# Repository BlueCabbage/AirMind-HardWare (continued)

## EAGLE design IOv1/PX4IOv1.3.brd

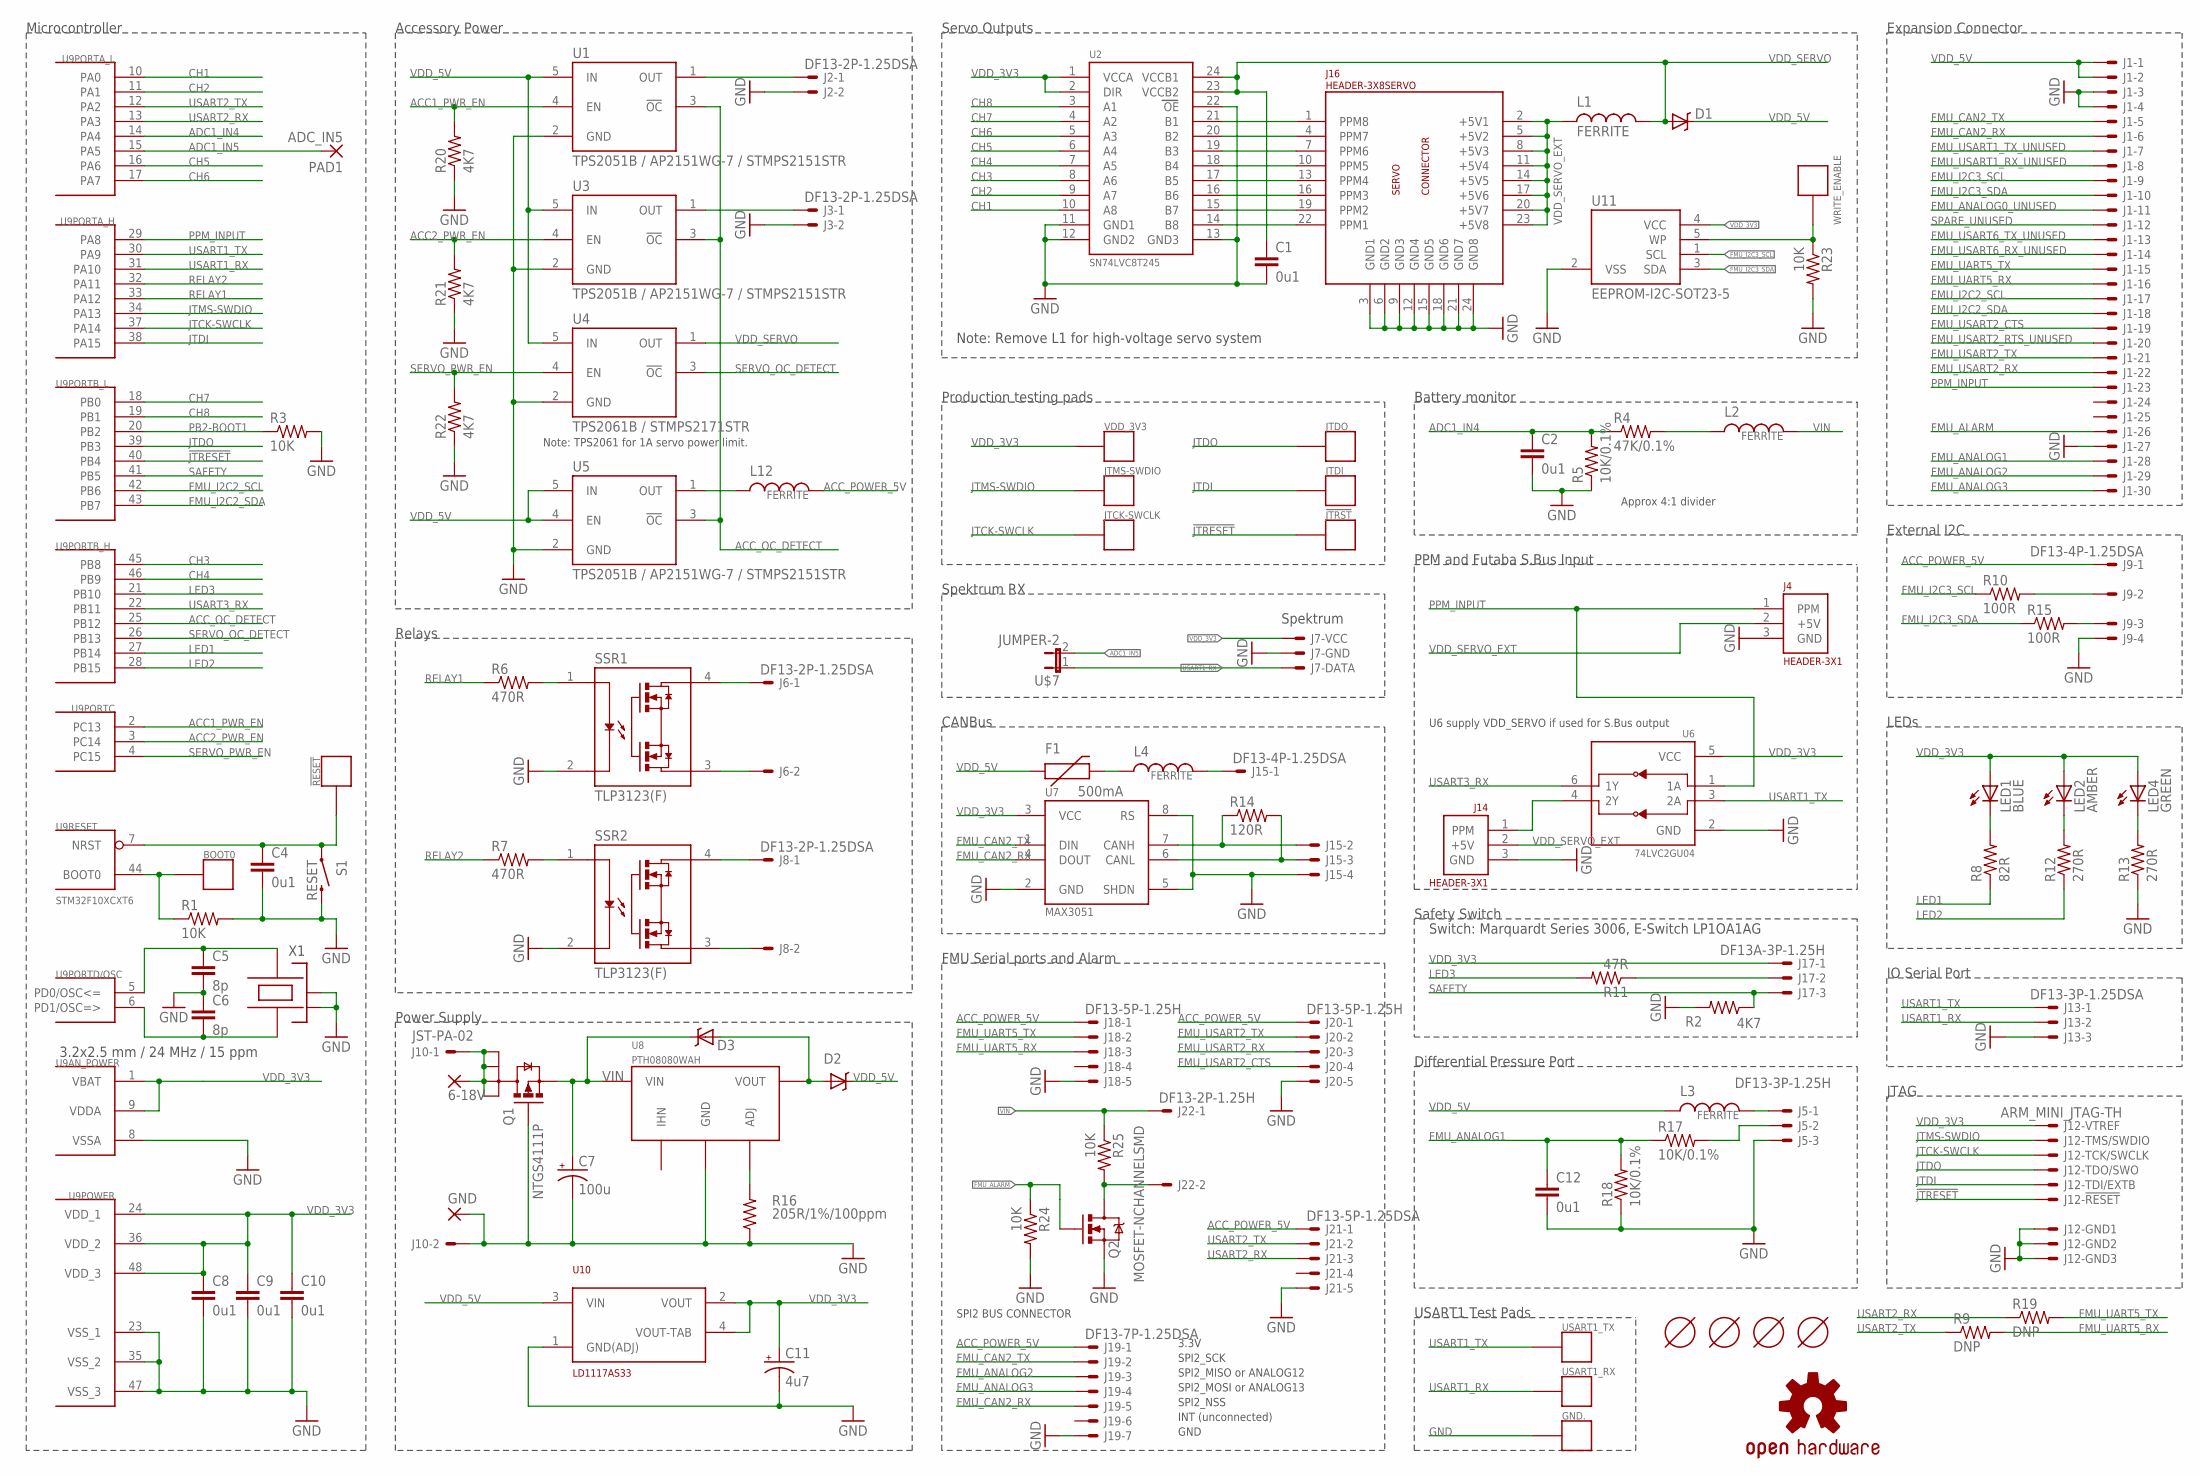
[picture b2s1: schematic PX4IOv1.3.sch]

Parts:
6-18V: WIREPADSMD3,5-2; 3,5-2; PARTNO *
!JTRST: PAD.04; PAD.04X.04; PARTNO *
!RESET: PAD.03; PAD.03X.03; PARTNO *
BOOT0: PAD.04; PAD.04X.04; PARTNO *
C1, C2, C4, C8, C9, C10, C12: 0u1; 0402-CAP; PARTNO CC0402ZRY5V7BB104
C5, C6: 8p; 0402-CAP; PARTNO C1005C0G1H080C
C7: 100u; EIA7343; PARTNO T491X107K025ZT
C11: 4u7; EIA3216; PARTNO T491A475K010AT
D1, D2: BAT 60A E6327; MICROSMP; PARTNO BAT 60A E6327
D3: MSS1P4-M3/89A; MICROSMP; PARTNO MSS1P4-M3/89A
F1: 500mA; 0603; PARTNO MF-FSMF050X-2
GND: WIREPADSMD3,5-2; 3,5-2; PARTNO *
GND.: PAD.04; PAD.04X.04; PARTNO *
J1: HEADER_2X15-REV; HEADER_2MM_2X15_REVERSE; PARTNO 951230-2520-AR-PR
J2, J3, J6, J8: DF13-2P-1.25DSA; PARTNO DF13-2P-1.25DSA
J4, J14: HEADER-3X1; 3X1RA; PARTNO 53047-02
J5: DF13-3P-1.25H; DF13A-3P-1.25H; PARTNO DF13-3P-1.25H(20)
J7: CONN_SPEKTRUM_RX-TH; B3B-ZR; PARTNO B3B-ZR
J9, J15: DF13-4P-1.25DSA; PARTNO DF13-4P-1.25DSA
J10: JST-PA-02; S02B-PASK-2; PARTNO S02B-PASK-2
J12: ARM_MINI_JTAG-TH; FTSH-105-01-XXX-DV; PARTNO M50-3900542
J13: DF13-3P-1.25DSA; PARTNO DF13-3P-1.25DSA
J16: HEADER-3X8SERVO; 3X8RA; PARTNO *
J17: DF13A-3P-1.25H; PARTNO DF13A-3P-1.25H(20)
J18, J20: DF13-5P-1.25H; DF13A-5P-1.25H; PARTNO DF13A-5P-1.25H(20)
J19: DF13-7P-1.25DSA; PARTNO DF13-7P-1.25DSA(20)
J21: DF13-5P-1.25DSA; PARTNO DF13-5P-1.25DSA(20)
J22: DF13-2P-1.25H; DF13A-2P-1.25H; PARTNO DF13-2P-1.25H(20)
JTCK-SWCLK: PAD.04; PAD.04X.04; PARTNO *
JTDI: PAD.04; PAD.04X.04; PARTNO *
JTDO: PAD.04; PAD.04X.04; PARTNO *
JTMS-SWDIO: PAD.04; PAD.04X.04; PARTNO *
L1, L2, L3, L4, L12: FERRITE; 0402-IND; PARTNO BKP1005HS121-T
LED1: BLUE; LED-0603; PARTNO LNJ937W8CRA
LED2: AMBER; LED-0603; PARTNO LNJ437W84RA
LED4: GREEN; LED-0603; PARTNO LNJ337W83RA
PAD1: ADC_IN5; PAD-2.5-1.8
Q1: NTGS4111P; TSOP-6; PARTNO NTGS4111P
Q2: MOSFET-NCHANNELSMD; SOT23-3; PARTNO ZXMS6004FFTA
R1, R3, R23, R24, R25: 10K; 0402-RES; PARTNO RMCF0402FT10K0
R2, R20, R21, R22: 4K7; 0402-RES; PARTNO RMCF0402JT4K70
R4: 47K/0.1%; 0402-RES; PARTNO RC0402FR-0747KL
R5, R17, R18: 10K/0.1%; 0402-RES; PARTNO RMCF0402FT10K0
R6, R7: 470R; 0402-RES; PARTNO RMCF0402JT470R
R8: 82R; 0402-RES; PARTNO MCR01MZPJ820
R9, R19: DNP; 0402-RES; PARTNO RMCF0402FT10K0
R10, R15: 100R; 0402-RES; PARTNO RMCF0402JT100R
R11: 47R; 0402-RES; PARTNO RMCF0402JT47R0
R12, R13: 270R; 0402-RES; PARTNO MCR01MZPJ271
R14: 120R; 0402-RES; PARTNO P120JCT-ND
R16: 205R/1%/100ppm; 0402-RES; PARTNO ERJ-2RKF2050X
S1: RESET; EVQP7J01K; PARTNO EVQP7J01K
SSR1, SSR2: TLP3123(F); SOP4-2.54; PARTNO TLP3123(F)
U1, U3, U5: TPS2051B / AP2151WG-7 / STMPS2151STR; SOT23-5L; PARTNO AP2151WG-7
U2: SN74LVC8T245; R-PDSO-G24; PARTNO SN74LVC8T245DBQR
U4: TPS2061B / STMPS2171STR; SOT23-5L; PARTNO STMPS2171STR
U6: 74LVC2GU04; SOT363_PHILIPS; PARTNO 74LVC2GU04GW,125
U7: MAX3051; SO08; PARTNO MAX3051ESA+
U8: PTH08080WAH; PTH08080W_TH; PARTNO PTH08080WAH
U9: STM32F10XCXT6; TQFP48; PARTNO STM32F100C8T6B
U10: LD1117AS33; SOT-223; PARTNO LD1117AS33
U11: EEPROM-I2C-SOT23-5; SOT23-5; PARTNO 24LC01BT-I/OT
U$1: OSHW-LOGOS; OSHW-LOGO-S
U$2, U$3, U$4, U$5: MOUNT-HOLE3.1MM; MOUNT-HOLE3.1; PARTNO *
U$7: JUMPER-2; SJ_2
USART1_RX, USART1_TX: PAD.04; PAD.04X.04; PARTNO *
VDD_3V3: PAD.04; PAD.04X.04; PARTNO *
WRITE_ENABLE: PAD.04; PAD.04X.04; PARTNO *
X1: 3.2x2.5 mm / 24 MHz / 15 ppm; OSCILLATOR-3.2X2.5; PARTNO NX3225SA-24.000000MHZ

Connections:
!JTRESET: !JTRST.P$1, J12.10, U9.40 (PB4)
ACC1_PWR_EN: R20.2, U1.4 (EN), U9.2 (PC13)
ACC2_PWR_EN: R21.2, U3.4 (EN), U9.3 (PC14)
ACC_OC_DETECT: U1.3 (!OC), U3.3 (!OC), U5.3 (!OC), U9.25 (PB12)
ACC_POWER_5V: J9.1, J18.1, J19.1, J20.1, J21.1, L12.2
ADC1_IN4: C2.1, R4.1, R5.2, U9.14 (PA4)
ADC1_IN5: PAD1.P$1, U9.15 (PA5), U$7.2
BOOT0: BOOT0.P$1, R1.1, U9.44 (BOOT0)
CH1: U2.10 (A8), U9.10 (PA0)
CH2: U2.9 (A7), U9.11 (PA1)
CH3: U2.8 (A6), U9.45 (PB8)
CH4: U2.7 (A5), U9.46 (PB9)
CH5: U2.6 (A4), U9.16 (PA6)
CH6: U2.5 (A3), U9.17 (PA7)
CH7: U2.4 (A2), U9.18 (PB0)
CH8: U2.3 (A1), U9.19 (PB1)
FMU_ALARM: J1.26, Q2.1 (G), R24.1
FMU_ANALOG0_UNUSED: J1.11
FMU_ANALOG1: C12.1, J1.28, R17.1, R18.2
FMU_ANALOG2: J1.29, J19.3
FMU_ANALOG3: J1.30, J19.4
FMU_CAN2_RX: J1.6, J19.5, U7.4 (DOUT)
FMU_CAN2_TX: J1.5, J19.2, U7.1 (DIN)
FMU_I2C2_SCL: J1.17, U9.42 (PB6)
FMU_I2C2_SDA: J1.18, U9.43 (PB7)
FMU_I2C3_SCL: J1.9, R10.1, U11.1 (SCL)
FMU_I2C3_SDA: J1.10, R15.1, U11.3 (SDA)
FMU_UART5_RX: J1.16, J18.3, R9.2
FMU_UART5_TX: J1.15, J18.2, R19.2
FMU_USART1_RX_UNUSED: J1.8
FMU_USART1_TX_UNUSED: J1.7
FMU_USART2_CTS: J1.19, J20.4
FMU_USART2_RTS_UNUSED: J1.20
FMU_USART2_RX: J1.22, J20.3
FMU_USART2_TX: J1.21, J20.2
FMU_USART6_RX_UNUSED: J1.14
FMU_USART6_TX_UNUSED: J1.13
GND: C1.2, C2.2, C4.2, C5.2, C6.1, C7.C (-), C8.2, C9.2, C10.2, C11.C (-), C12.2, GND.1, GND..P$1, J1.3, J1.4, J1.27, J2.2, J3.2, J4.3 (GND), J5.3, J7.2, J9.4, J10.2, J12.3, J12.5, J12.9, J13.3, J14.3 (GND), J15.4, J16.3 (GND1), J16.6 (GND2), J16.9 (GND3), J16.12 (GND4), J16.15 (GND5), J16.18 (GND6), J16.21 (GND7), J16.24 (GND8), J18.5, J19.7, J20.5, J21.5, Q1.3 (G), Q2.2 (S), R1.2, R2.2, R3.2, R5.1, R13.1, R16.1, R18.1, R20.1, R21.1, R22.1, R23.2, R24.2, S1.B3 (2), SSR1.2, SSR2.2, U1.2 (GND), U2.11 (GND1), U2.12 (GND2), U2.13 (GND3), U2.22 (OE), U3.2 (GND), U4.2 (GND), U5.2 (GND), U6.2 (GND), U7.2 (GND), U7.5 (SHDN), U7.8 (RS), U8.2 (GND), U9.8 (VSSA), U9.23 (VSS_1), U9.35 (VSS_2), U9.47 (VSS_3), U10.1 (GND(ADJ)), U11.2 (VSS), X1.2 (NC_2), X1.4 (NC_4)
JTCK-SWCLK: J12.4, JTCK-SWCLK.P$1, U9.37 (PA14)
JTDI: J12.8, JTDI.P$1, U9.38 (PA15)
JTDO: J12.6, JTDO.P$1, U9.39 (PB3)
JTMS-SWDIO: J12.2, JTMS-SWDIO.P$1, U9.34 (PA13)
LED1: R8.1, U9.27 (PB14)
LED2: R12.1, U9.28 (PB15)
LED3: R11.2, U9.21 (PB10)
unnamed: R7.2, SSR2.1
unnamed: R6.2, SSR1.1
unnamed: J14.1 (PPM), U6.4 (2Y)
unnamed: L12.1, U5.1 (OUT)
unnamed: C6.2, U9.6 (PD1/OSC=>), X1.1
unnamed: C5.1, U9.5 (PD0/OSC<=), X1.3
unnamed: L2.1, R4.2
unnamed: LED1.C, R8.2
unnamed: R16.2, U8.4 (ADJ)
unnamed: J17.2, R11.1
unnamed: R23.1, U11.5 (WP), WRITE_ENABLE.P$1
unnamed: J22.2, Q2.3 (D), R25.2
unnamed: F1.2, L4.1
unnamed: J5.2, R17.2
unnamed: J8.1, SSR2.4
unnamed: J8.2, SSR2.3
unnamed: J6.2, SSR1.3
unnamed: J6.1, SSR1.4
unnamed: J9.3, R15.2
unnamed: J9.2, R10.2
unnamed: J2.1, U1.1 (OUT)
unnamed: J3.1, U3.1 (OUT)
unnamed: LED2.C, R12.2
unnamed: LED4.C, R13.2
unnamed: J15.2, R14.1, U7.7 (CANH)
unnamed: J15.3, R14.2, U7.6 (CANL)
unnamed: J15.1, L4.2
NRST: !RESET.P$1, C4.1, S1.A1 (1), U9.7 (NRST)
PB2-BOOT1: R3.1, U9.20 (PB2)
PPM1: J16.22 (PPM1), U2.14 (B8)
PPM2: J16.19 (PPM2), U2.15 (B7)
PPM3: J16.16 (PPM3), U2.16 (B6)
PPM4: J16.13 (PPM4), U2.17 (B5)
PPM5: J16.10 (PPM5), U2.18 (B4)
PPM6: J16.7 (PPM6), U2.19 (B3)
PPM7: J16.4 (PPM7), U2.20 (B2)
PPM8: J16.1 (PPM8), U2.21 (B1)
PPM_INPUT: J1.23, J4.1 (PPM), U6.1 (1A), U9.29 (PA8)
RELAY1: R6.1, U9.33 (PA12)
RELAY2: R7.1, U9.32 (PA11)
SAFETY: J17.3, R2.1, U9.41 (PB5)
SERVO_OC_DETECT: U4.3 (!OC), U9.26 (PB13)
SERVO_PWR_EN: R22.2, U4.4 (EN), U9.4 (PC15)
SPARE_UNUSED: J1.12
USART1_RX: J7.1, J13.2, U9.31 (PA10), U$7.1, USART1_RX.P$1
USART1_TX: J13.1, U6.3 (2A), U9.30 (PA9), USART1_TX.P$1
USART2_RX: J21.3, R19.1, U9.13 (PA3)
USART2_TX: J21.2, R9.1, U9.12 (PA2)
USART3_RX: U6.6 (1Y), U9.22 (PB11)
VDD_3V3: C8.1, C9.1, C10.1, C11.A (+), J7.3, J12.1, J17.1, LED1.A, LED2.A, LED4.A, U2.1 (VCCA), U2.2 (DIR), U6.5 (VCC), U7.3 (VCC), U9.1 (VBAT), U9.9 (VDDA), U9.24 (VDD_1), U9.36 (VDD_2), U9.48 (VDD_3), U10.2 (VOUT), U10.4 (VOUT-TAB), U11.4 (VCC), VDD_3V3.P$1
VDD_5V: D1.CATHODE (C), D2.CATHODE (C), F1.1, J1.1, J1.2, L3.1, U1.5 (IN), U3.5 (IN), U4.5 (IN), U5.4 (EN), U5.5 (IN), U10.3 (VIN)
VDD_5V_ANALOG: J5.1, L3.2
VDD_SERVO: C1.1, D1.ANODE (A), L1.2, U2.23 (VCCB2), U2.24 (VCCB1), U4.1 (OUT)
VDD_SERVO_EXT: J4.2 (+5V), J14.2 (+5V), J16.2 (+5V1), J16.5 (+5V2), J16.8 (+5V3), J16.11 (+5V4), J16.14 (+5V5), J16.17 (+5V6), J16.20 (+5V7), J16.23 (+5V8), L1.1
VIN: C7.A (+), D3.CATHODE (C), J22.1, L2.2, Q1.4 (S), R25.1, U8.1 (VIN)
VIN_CONTACT: 6-18V.1, J10.1, Q1.1 (D), Q1.2 (D1), Q1.5 (D2), Q1.6 (D3)
VOUT: D2.ANODE (A), D3.ANODE (A), U8.3 (VOUT)

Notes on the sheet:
Note: Remove L1 for high-voltage servo system
Spektrum
Accessory Power
Relays
Power Supply
Servo Outputs
CANBus
Production testing pads
External I2C
Spektrum RX
JTAG
LEDs
FMU Serial ports and Alarm
Expansion Connector
Microcontroller
Note: TPS2061 for 1A servo power limit.
PPM and Futaba S.Bus Input
Differential Pressure Port
Battery monitor
Approx 4:1 divider
U6 supply VDD_SERVO if used for S.Bus output
IO Serial Port
USART1 Test Pads
Safety Switch
Switch: Marquardt Series 3006, E-Switch LP1OA1AG
3.3V
SPI2_SCK
SPI2_MISO or ANALOG12
SPI2_MOSI or ANALOG13
SPI2_NSS
GND
SPI2 BUS CONNECTOR
INT (unconnected)

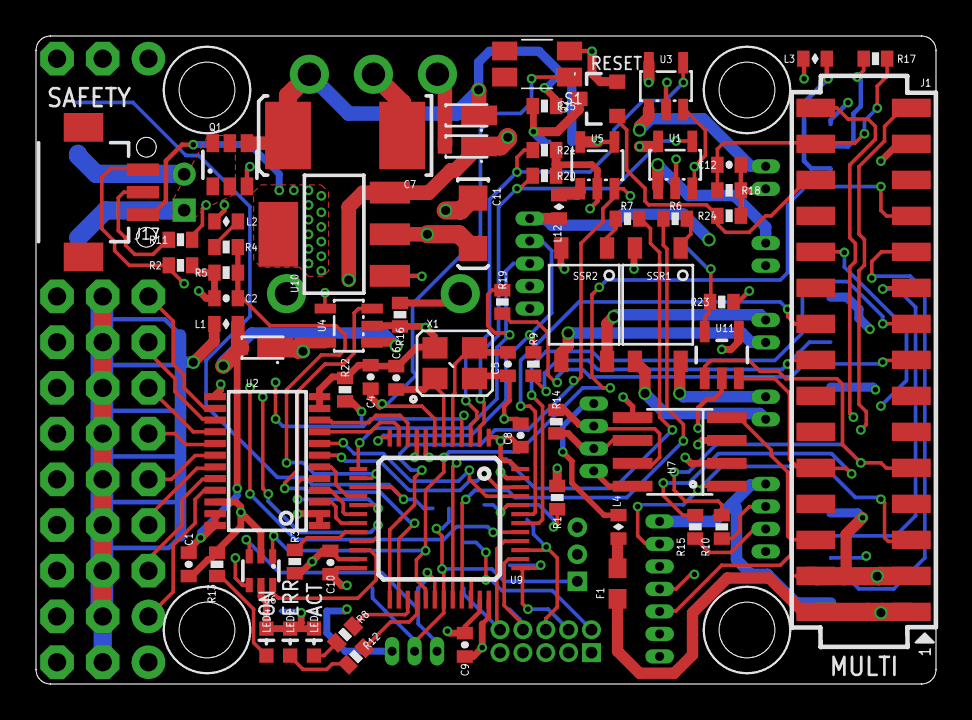
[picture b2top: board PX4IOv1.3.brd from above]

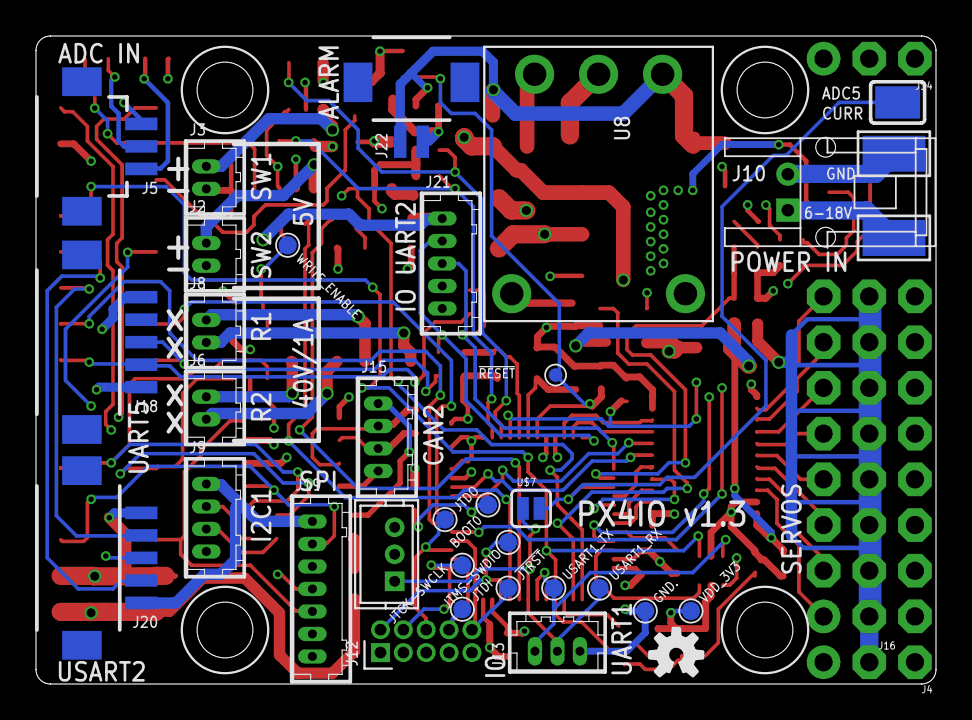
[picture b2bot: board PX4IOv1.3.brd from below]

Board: 4 copper layers, 50.0 x 36.0 mm, 107 parts (37 on the bottom side), 95 nets.

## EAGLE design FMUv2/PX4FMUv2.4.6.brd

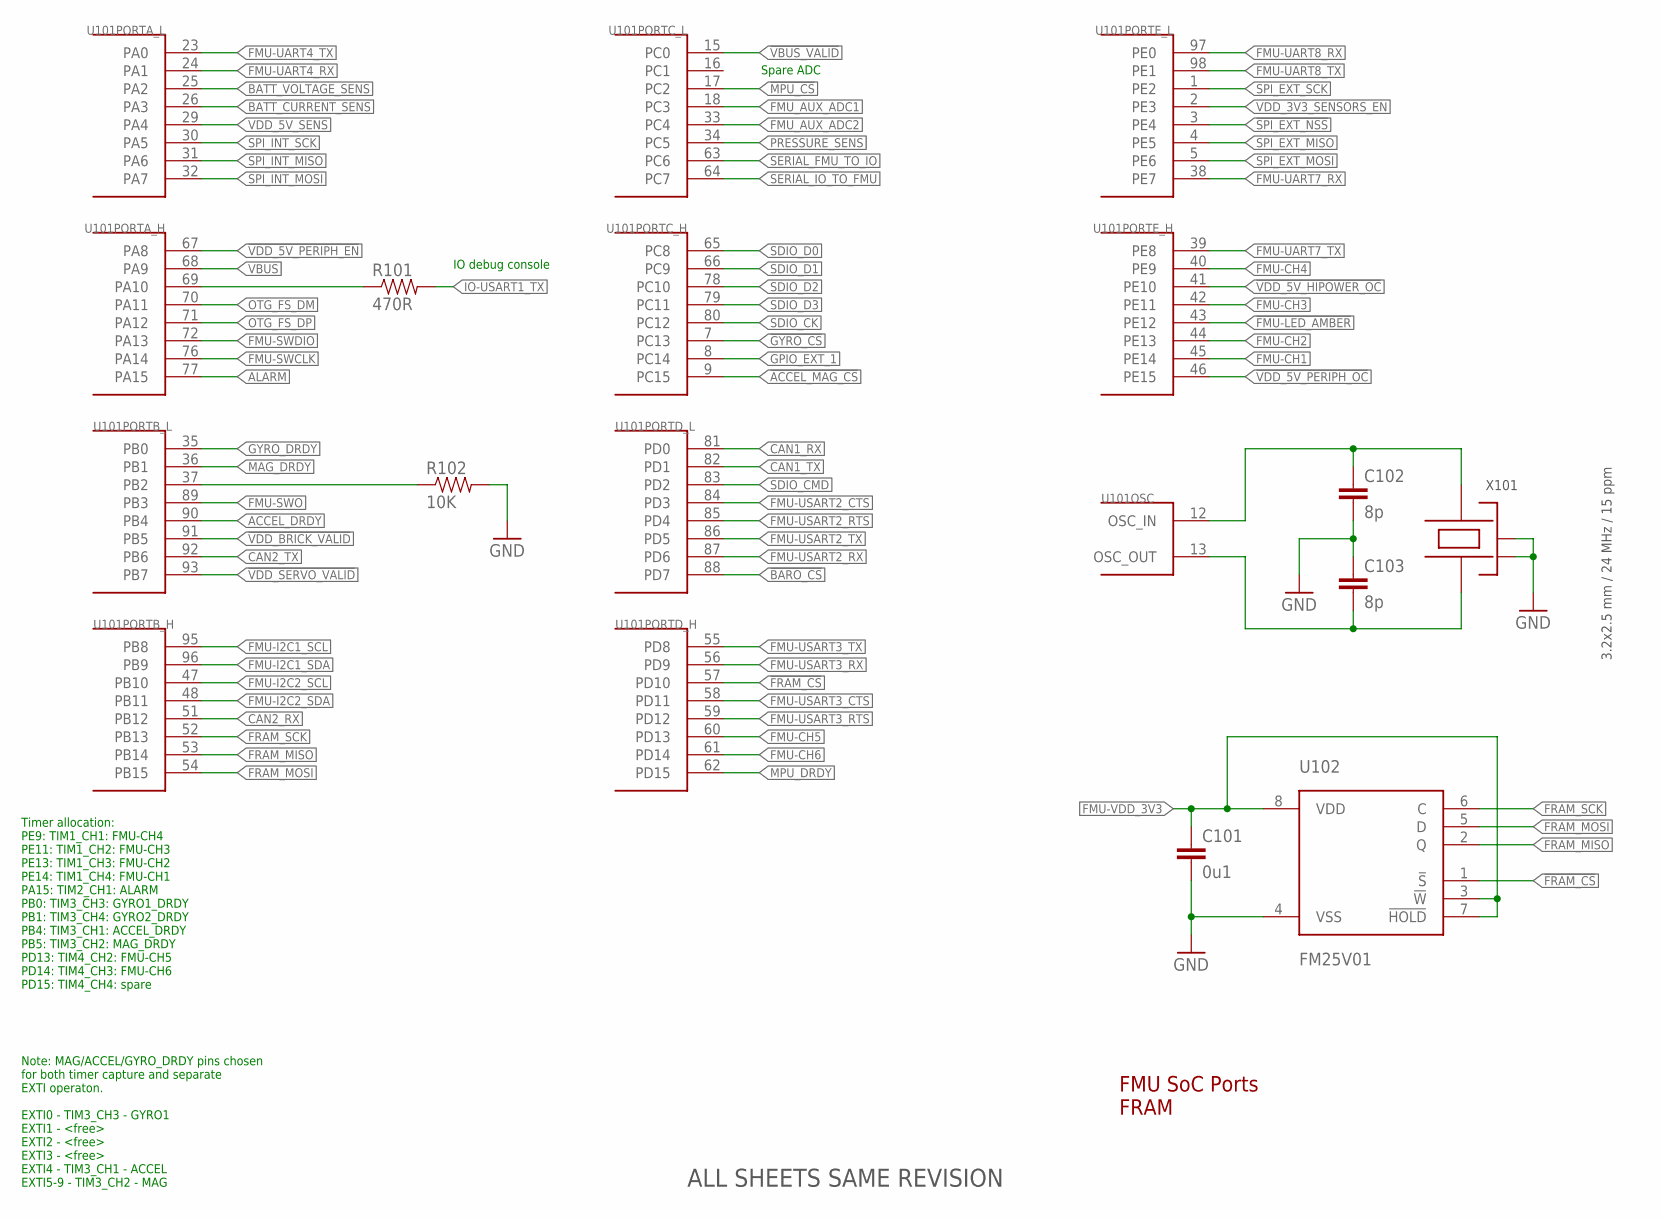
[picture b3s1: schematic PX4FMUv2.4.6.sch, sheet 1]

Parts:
C101: 0u1; 0402-CAP; PARTNO CC0402ZRY5V7BB104
C102, C103: 8p; 0402-CAP; PARTNO C1005C0G1H080C
R101: 470R; 0402-RES; PARTNO RC0402FR-07470RL
R102: 10K; 0402-RES; PARTNO RC0402FR-0710KL
U101: STM32F4X7VX; TQFP100; PARTNO STM32F427VI
U102: FM25V01; SO08; PARTNO FM25V01-G
X101: 3.2x2.5 mm / 24 MHz / 15 ppm; OSCILLATOR-3.2X2.5; PARTNO NX3225SA-24.000000MHZ

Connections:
!ACCEL_MAG_CS: U101.9 (PC15); also elsewhere on the board
!BARO_CS: U101.88 (PD7); also elsewhere on the board
!FMU-LED_AMBER: U101.43 (PE12); also elsewhere on the board
!FRAM_CS: U101.57 (PD10), U102.1 (!S)
!GYRO_CS: U101.7 (PC13); also elsewhere on the board
!MPU_CS: U101.17 (PC2); also elsewhere on the board
!SPI_EXT_NSS: U101.3 (PE4); also elsewhere on the board
!VBUS_VALID: U101.15 (PC0); also elsewhere on the board
!VDD_5V_HIPOWER_OC: U101.41 (PE10); also elsewhere on the board
!VDD_5V_PERIPH_EN: U101.67 (PA8); also elsewhere on the board
!VDD_5V_PERIPH_OC: U101.46 (PE15); also elsewhere on the board
!VDD_BRICK_VALID: U101.91 (PB5); also elsewhere on the board
!VDD_SERVO_VALID: U101.93 (PB7); also elsewhere on the board
ACCEL_DRDY: U101.90 (PB4); also elsewhere on the board
ALARM: U101.77 (PA15); also elsewhere on the board
BATT_CURRENT_SENS: U101.26 (PA3); also elsewhere on the board
BATT_VOLTAGE_SENS: U101.25 (PA2); also elsewhere on the board
CAN1_RX: U101.81 (PD0); also elsewhere on the board
CAN1_TX: U101.82 (PD1); also elsewhere on the board
CAN2_RX: U101.51 (PB12); also elsewhere on the board
CAN2_TX: U101.92 (PB6); also elsewhere on the board
FMU-CH1: U101.45 (PE14); also elsewhere on the board
FMU-CH2: U101.44 (PE13); also elsewhere on the board
FMU-CH3: U101.42 (PE11); also elsewhere on the board
FMU-CH4: U101.40 (PE9); also elsewhere on the board
FMU-CH5: U101.60 (PD13); also elsewhere on the board
FMU-CH6: U101.61 (PD14); also elsewhere on the board
FMU-I2C1_SCL: U101.95 (PB8); also elsewhere on the board
FMU-I2C1_SDA: U101.96 (PB9); also elsewhere on the board
FMU-I2C2_SCL: U101.47 (PB10); also elsewhere on the board
FMU-I2C2_SDA: U101.48 (PB11); also elsewhere on the board
FMU-SWCLK: U101.76 (PA14); also elsewhere on the board
FMU-SWDIO: U101.72 (PA13); also elsewhere on the board
FMU-SWO: U101.89 (PB3); also elsewhere on the board
FMU-UART4_RX: U101.24 (PA1); also elsewhere on the board
FMU-UART4_TX: U101.23 (PA0); also elsewhere on the board
FMU-UART7_RX: U101.38 (PE7); also elsewhere on the board
FMU-UART7_TX: U101.39 (PE8); also elsewhere on the board
FMU-UART8_RX: U101.97 (PE0); also elsewhere on the board
FMU-UART8_TX: U101.98 (PE1); also elsewhere on the board
FMU-USART2_CTS: U101.84 (PD3); also elsewhere on the board
FMU-USART2_RTS: U101.85 (PD4); also elsewhere on the board
FMU-USART2_RX: U101.87 (PD6); also elsewhere on the board
FMU-USART2_TX: U101.86 (PD5); also elsewhere on the board
FMU-USART3_CTS: U101.58 (PD11); also elsewhere on the board
FMU-USART3_RTS: U101.59 (PD12); also elsewhere on the board
FMU-USART3_RX: U101.56 (PD9); also elsewhere on the board
FMU-USART3_TX: U101.55 (PD8); also elsewhere on the board
FMU-VDD_3V3: C101.P$1 (1), U102.3 (!W), U102.7 (!HOLD), U102.8 (VDD); also elsewhere on the board
FMU_AUX_ADC1: U101.18 (PC3); also elsewhere on the board
FMU_AUX_ADC2: U101.33 (PC4); also elsewhere on the board
FRAM_MISO: U101.53 (PB14), U102.2 (Q)
FRAM_MOSI: U101.54 (PB15), U102.5 (D)
FRAM_SCK: U101.52 (PB13), U102.6 (C)
GND: C101.P$2 (2), C102.P$2 (2), C103.P$1 (1), R102.P$2 (2), U102.4 (VSS), X101.2 (NC_2), X101.4 (NC_4); also elsewhere on the board
GPIO_EXT_1: U101.8 (PC14); also elsewhere on the board
GYRO_DRDY: U101.35 (PB0); also elsewhere on the board
IO-USART1_TX: R101.P$2 (2); also elsewhere on the board
MAG_DRDY: U101.36 (PB1); also elsewhere on the board
MPU_DRDY: U101.62 (PD15); also elsewhere on the board
unnamed: C103.P$2 (2), U101.13 (OSC_OUT), X101.1
unnamed: C102.P$1 (1), U101.12 (OSC_IN), X101.3
unnamed: R101.P$1 (1), U101.69 (PA10)
OTG_FS_DM: U101.70 (PA11); also elsewhere on the board
OTG_FS_DP: U101.71 (PA12); also elsewhere on the board
PB2-BOOT1: R102.P$1 (1), U101.37 (PB2)
PRESSURE_SENS: U101.34 (PC5); also elsewhere on the board
SDIO_CK: U101.80 (PC12); also elsewhere on the board
SDIO_CMD: U101.83 (PD2); also elsewhere on the board
SDIO_D0: U101.65 (PC8); also elsewhere on the board
SDIO_D1: U101.66 (PC9); also elsewhere on the board
SDIO_D2: U101.78 (PC10); also elsewhere on the board
SDIO_D3: U101.79 (PC11); also elsewhere on the board
SERIAL_FMU_TO_IO: U101.63 (PC6); also elsewhere on the board
SERIAL_IO_TO_FMU: U101.64 (PC7); also elsewhere on the board
SPI_EXT_MISO: U101.4 (PE5); also elsewhere on the board
SPI_EXT_MOSI: U101.5 (PE6); also elsewhere on the board
SPI_EXT_SCK: U101.1 (PE2); also elsewhere on the board
SPI_INT_MISO: U101.31 (PA6); also elsewhere on the board
SPI_INT_MOSI: U101.32 (PA7); also elsewhere on the board
SPI_INT_SCK: U101.30 (PA5); also elsewhere on the board
VBUS: U101.68 (PA9); also elsewhere on the board
VDD_3V3_SENSORS_EN: U101.2 (PE3); also elsewhere on the board
VDD_5V_SENS: U101.29 (PA4); also elsewhere on the board

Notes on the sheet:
FMU SoC Ports FRAM
Note: MAG/ACCEL/GYRO_DRDY pins chosen for both timer capture and separate EXTI operaton. EXTI0 - TIM3_CH3 - GYRO1 EXTI1 - <free> EXTI2 - <free> EXTI3 - <free> EXTI4 - TIM3_CH1 - ACCEL EXTI5-9 - TIM3_CH2 - MAG
Timer allocation: PE9: TIM1_CH1: FMU-CH4 PE11: TIM1_CH2: FMU-CH3 PE13: TIM1_CH3: FMU-CH2 PE14: TIM1_CH4: FMU-CH1 PA15: TIM2_CH1: ALARM PB0: TIM3_CH3: GYRO1_DRDY PB1: TIM3_CH4: GYRO2_DRDY PB4: TIM3_CH1: ACCEL_DRDY PB5: TIM3_CH2: MAG_DRDY PD13: TIM4_CH2: FMU-CH5 PD14: TIM4_CH3: FMU-CH6 PD15: TIM4_CH4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
IO debug console
Spare ADC
ALL SHEETS SAME REVISION

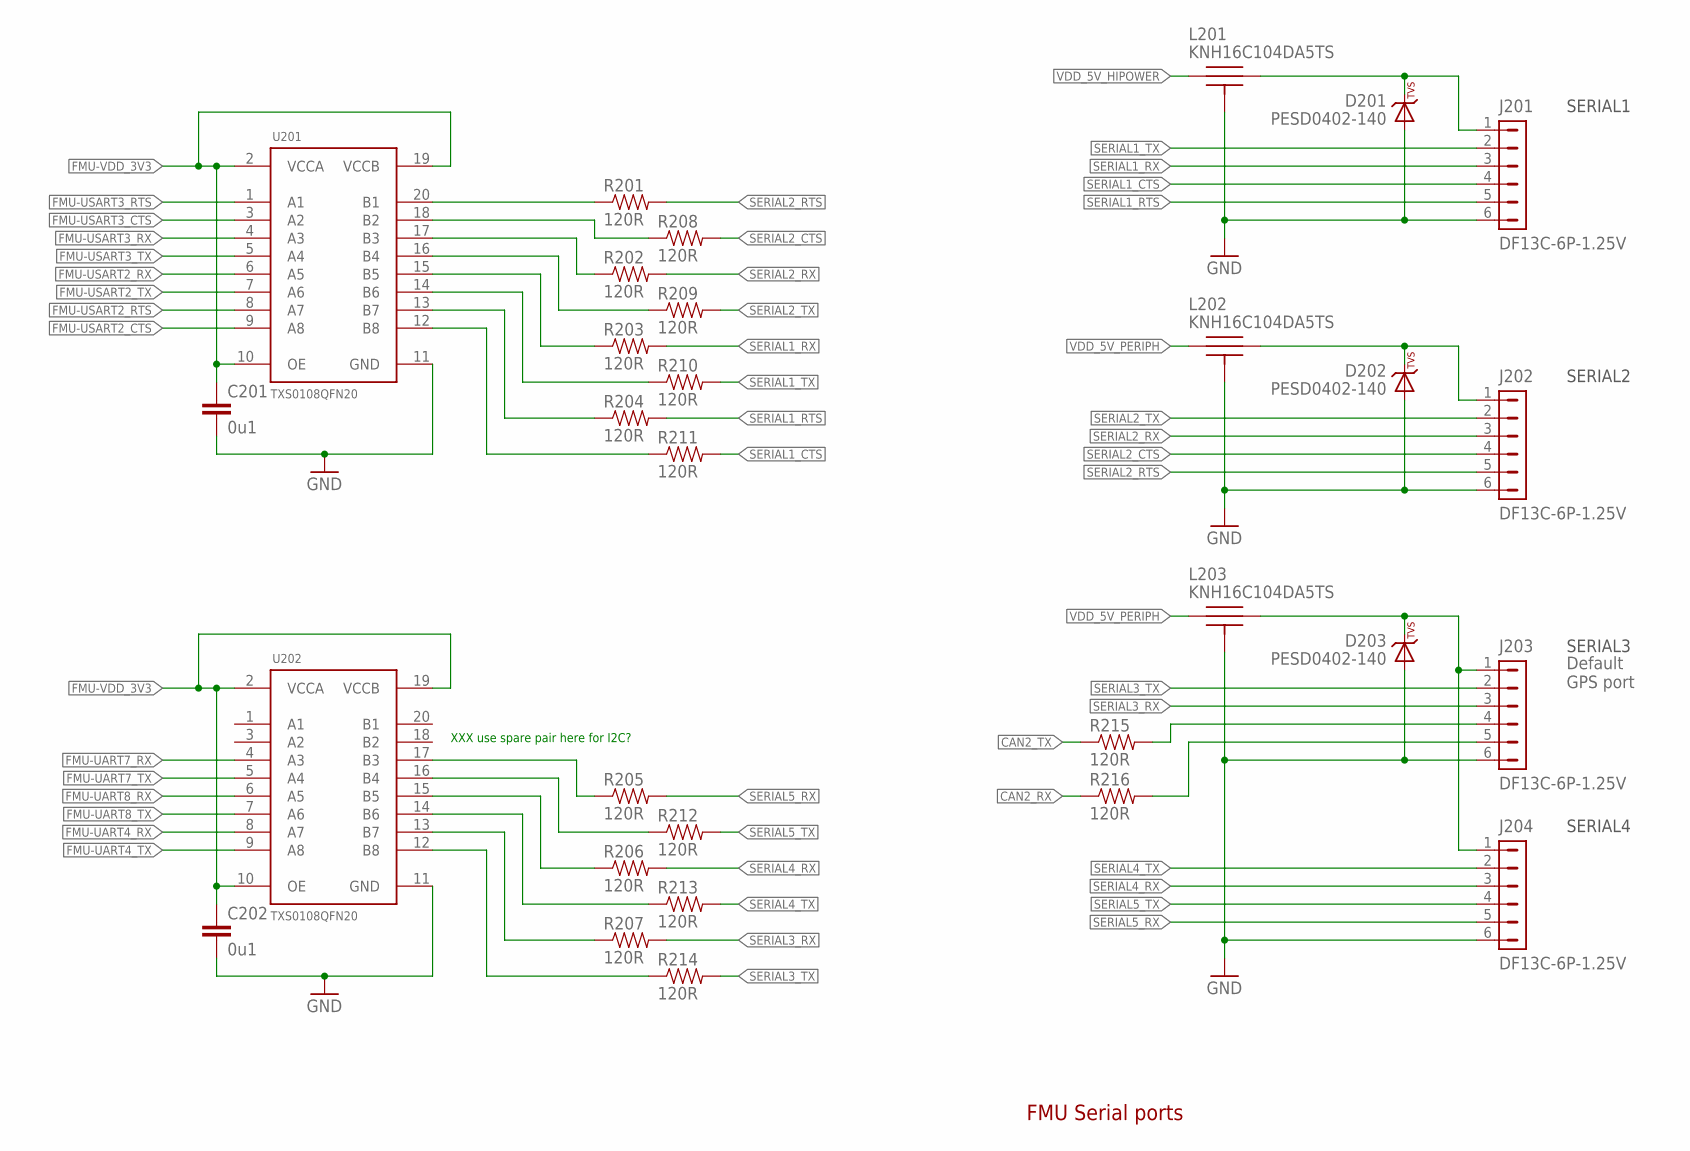
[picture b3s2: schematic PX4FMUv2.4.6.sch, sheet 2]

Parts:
C201, C202: 0u1; 0402-CAP; PARTNO CC0402ZRY5V7BB104
D201, D202, D203: PESD0402-140; 0402-TVS; PARTNO PESD0402-140
J201, J202, J203, J204: DF13C-6P-1.25V; PARTNO DF13C-6P-1.25V(20)
L201, L202, L203: KNH16C104DA5TS; KYOCERA-KNH16-DA; PARTNO KNH16C104DA5TS
R201, R202, R203, R204, R205, R206, R207, R208, R209, R210, R211, R212, R213, R214, R215, R216: 120R; 0402-RES; PARTNO RC0402FR-07120RL
U201, U202: TXS0108QFN20; QFN20-RGY; PARTNO TXS0108ERGYR

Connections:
CAN2_RX: R216.P$1 (1); also elsewhere on the board
CAN2_TX: R215.P$1 (1); also elsewhere on the board
FMU-UART4_RX: U202.8 (A7); also elsewhere on the board
FMU-UART4_TX: U202.9 (A8); also elsewhere on the board
FMU-UART7_RX: U202.4 (A3); also elsewhere on the board
FMU-UART7_TX: U202.5 (A4); also elsewhere on the board
FMU-UART8_RX: U202.6 (A5); also elsewhere on the board
FMU-UART8_TX: U202.7 (A6); also elsewhere on the board
FMU-USART2_CTS: U201.9 (A8); also elsewhere on the board
FMU-USART2_RTS: U201.8 (A7); also elsewhere on the board
FMU-USART2_RX: U201.6 (A5); also elsewhere on the board
FMU-USART2_TX: U201.7 (A6); also elsewhere on the board
FMU-USART3_CTS: U201.3 (A2); also elsewhere on the board
FMU-USART3_RTS: U201.1 (A1); also elsewhere on the board
FMU-USART3_RX: U201.4 (A3); also elsewhere on the board
FMU-USART3_TX: U201.5 (A4); also elsewhere on the board
FMU-VDD_3V3: C201.P$1 (1), C202.P$1 (1), U201.2 (VCCA), U201.10 (OE), U201.19 (VCCB), U202.2 (VCCA), U202.10 (OE), U202.19 (VCCB); also elsewhere on the board
GND: C201.P$2 (2), C202.P$2 (2), D201.A, D202.A, D203.A, J201.6, J202.6, J203.6, J204.6, L201.P$3, L201.P$4, L201.P$5, L202.P$3, L202.P$4, L202.P$5, L203.P$3, L203.P$4, L203.P$5, U201.11 (GND), U202.11 (GND); also elsewhere on the board
unnamed: D201.C, J201.1, L201.P$2
unnamed: J203.4, R215.P$2 (2)
unnamed: J203.5, R216.P$2 (2)
unnamed: R201.P$1 (1), U201.20 (B1)
unnamed: R208.P$1 (1), U201.18 (B2)
unnamed: R202.P$1 (1), U201.17 (B3)
unnamed: R209.P$1 (1), U201.16 (B4)
unnamed: R203.P$1 (1), U201.15 (B5)
unnamed: R210.P$1 (1), U201.14 (B6)
unnamed: R204.P$1 (1), U201.13 (B7)
unnamed: R211.P$1 (1), U201.12 (B8)
unnamed: R207.P$1 (1), U202.13 (B7)
unnamed: R214.P$1 (1), U202.12 (B8)
unnamed: R205.P$1 (1), U202.17 (B3)
unnamed: R212.P$1 (1), U202.16 (B4)
unnamed: R206.P$1 (1), U202.15 (B5)
unnamed: R213.P$1 (1), U202.14 (B6)
unnamed: D203.C, J203.1, J204.1, L203.P$2
unnamed: D202.C, J202.1, L202.P$2
SERIAL1_CTS: J201.4, R211.P$2 (2)
SERIAL1_RTS: J201.5, R204.P$2 (2)
SERIAL1_RX: J201.3, R203.P$2 (2); also elsewhere on the board
SERIAL1_TX: J201.2, R210.P$2 (2); also elsewhere on the board
SERIAL2_CTS: J202.4, R208.P$2 (2)
SERIAL2_RTS: J202.5, R201.P$2 (2)
SERIAL2_RX: J202.3, R202.P$2 (2); also elsewhere on the board
SERIAL2_TX: J202.2, R209.P$2 (2); also elsewhere on the board
SERIAL3_RX: J203.3, R207.P$2 (2); also elsewhere on the board
SERIAL3_TX: J203.2, R214.P$2 (2); also elsewhere on the board
SERIAL4_RX: J204.3, R206.P$2 (2); also elsewhere on the board
SERIAL4_TX: J204.2, R213.P$2 (2); also elsewhere on the board
SERIAL5_RX: J204.5, R205.P$2 (2); also elsewhere on the board
SERIAL5_TX: J204.4, R212.P$2 (2); also elsewhere on the board
VDD_5V_HIPOWER: L201.P$1; also elsewhere on the board
VDD_5V_PERIPH: L202.P$1, L203.P$1; also elsewhere on the board

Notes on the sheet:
FMU Serial ports
XXX use spare pair here for I2C?
SERIAL2
SERIAL1
SERIAL3
SERIAL4
Default GPS port

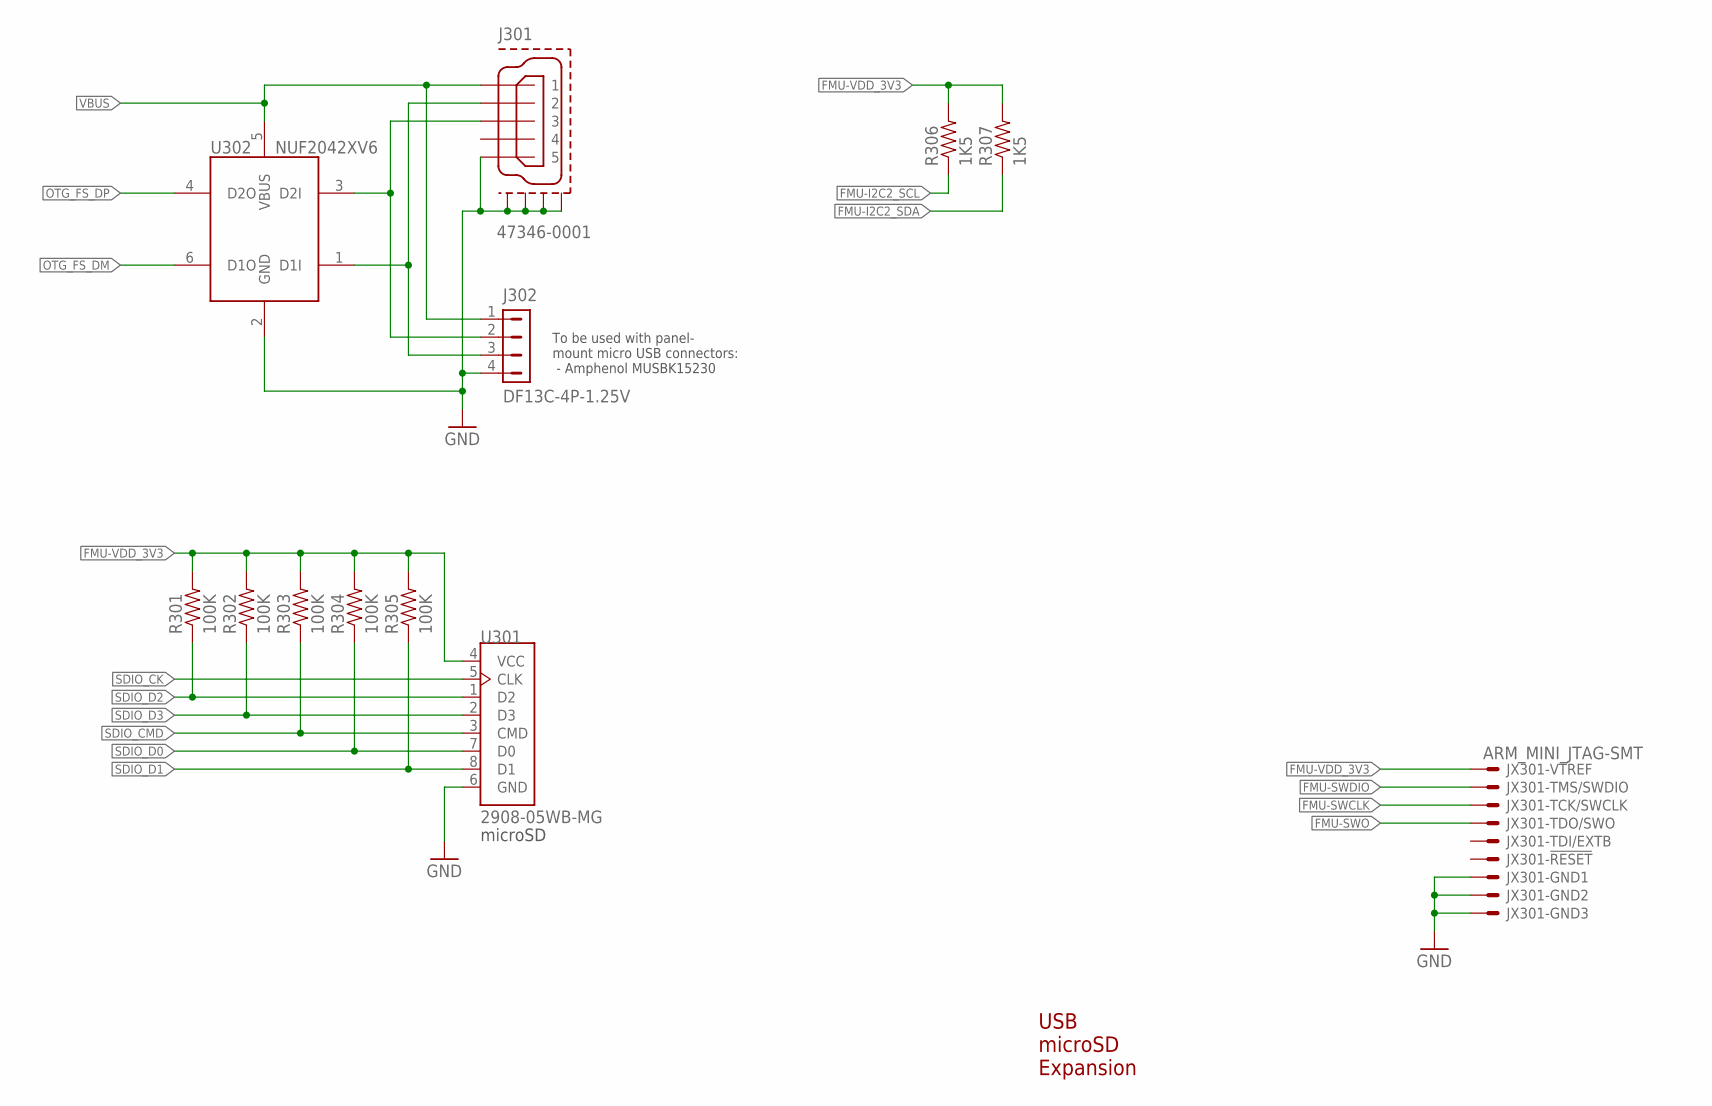
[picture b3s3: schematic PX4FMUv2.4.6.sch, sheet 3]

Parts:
J301: 47346-0001; MOLEX-47346-0001; PARTNO 47346-0001
J302: DF13C-4P-1.25V; PARTNO DF13C-4P-1.25V(20)
JX301: ARM_MINI_JTAG-SMT; FTSH-105-01-XXX-DV-K; PARTNO M50-3900542
R301, R302, R303, R304, R305: 100K; 0402-RES; PARTNO RC0402FR-07100KL
R306, R307: 1K5; 0402-RES; PARTNO RC0402FR-071K5L
U301: 2908-05WB-MG; MICROSD; PARTNO 2908-05WB-MG
U302: NUF2042XV6; SOT563-6; PARTNO NUF2042XV6T1G

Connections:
FMU-I2C2_SCL: R306.P$1 (1); also elsewhere on the board
FMU-I2C2_SDA: R307.P$1 (1); also elsewhere on the board
FMU-SWCLK: JX301.4; also elsewhere on the board
FMU-SWDIO: JX301.2; also elsewhere on the board
FMU-SWO: JX301.6; also elsewhere on the board
FMU-VDD_3V3: JX301.1, R301.P$2 (2), R302.P$2 (2), R303.P$2 (2), R304.P$2 (2), R305.P$2 (2), R306.P$2 (2), R307.P$2 (2), U301.4 (VCC); also elsewhere on the board
GND: J301.GND (5), J301.GND1, J301.GND2, J301.GND3, J301.GND4, J302.4, JX301.3, JX301.5, JX301.9, U301.6 (GND), U302.2 (GND); also elsewhere on the board
OTG_DM1: J301.D- (2), J302.3, U302.1 (D1I)
OTG_DP1: J301.D+ (3), J302.2, U302.3 (D2I)
OTG_FS_DM: U302.6 (D1O); also elsewhere on the board
OTG_FS_DP: U302.4 (D2O); also elsewhere on the board
SDIO_CK: U301.5 (CLK); also elsewhere on the board
SDIO_CMD: R303.P$1 (1), U301.3 (CMD); also elsewhere on the board
SDIO_D0: R304.P$1 (1), U301.7 (D0); also elsewhere on the board
SDIO_D1: R305.P$1 (1), U301.8 (D1); also elsewhere on the board
SDIO_D2: R301.P$1 (1), U301.1 (D2); also elsewhere on the board
SDIO_D3: R302.P$1 (1), U301.2 (D3); also elsewhere on the board
VBUS: J301.VBUS (1), J302.1, U302.5 (VBUS); also elsewhere on the board

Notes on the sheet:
USB microSD Expansion
microSD
To be used with panel- mount micro USB connectors: - Amphenol MUSBK15230
